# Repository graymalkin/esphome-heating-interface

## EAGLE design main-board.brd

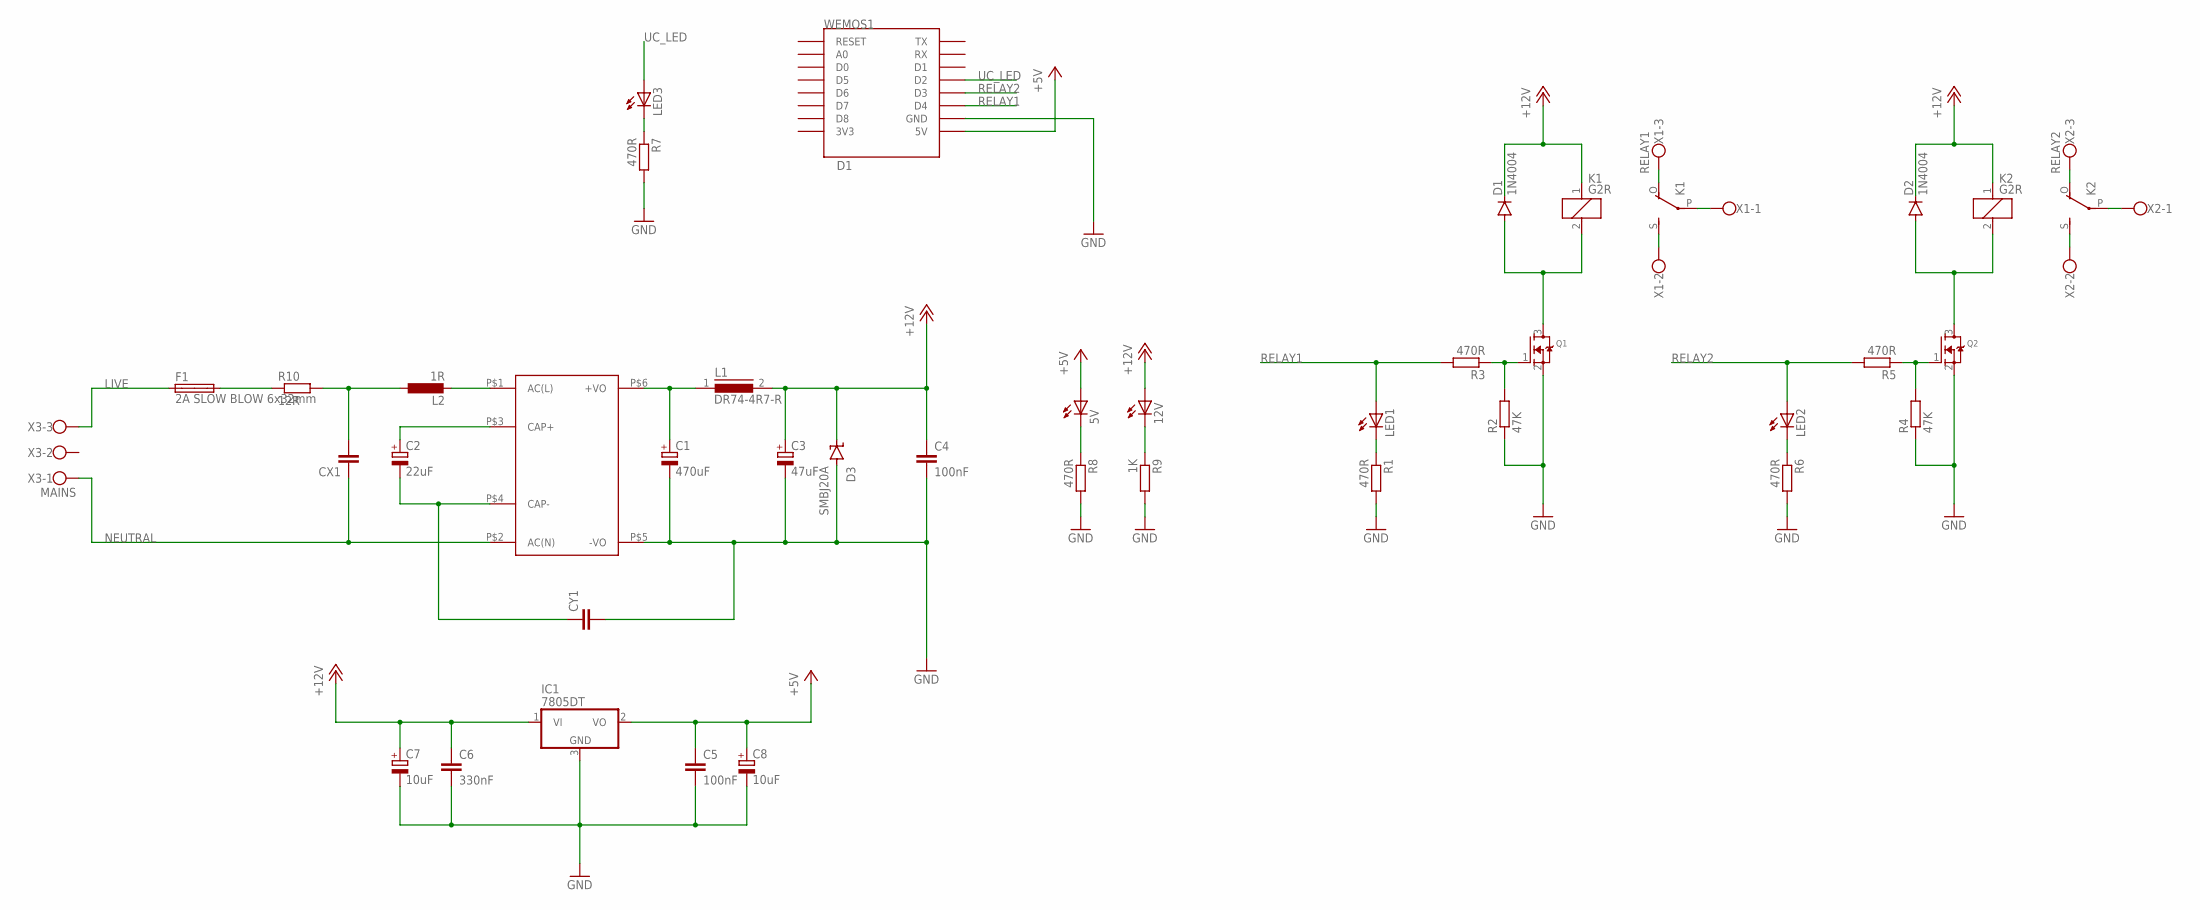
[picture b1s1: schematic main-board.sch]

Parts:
5V, 12V: LEDSMT1206; 1206
C1: 470uF; PANASONIC_E
C2: 22uF; E7,5-16
C3: 47uF; PANASONIC_D
C4, C5: 100nF; C0603
C6: 330nF; C0603
C7, C8: 10uF; PANASONIC_B
CX1: CXXC15B8; XC15B8
CY1: CYYC10B5; YC10B5
D1, D2: 1N4004; DO41-10
D3: SMBJ20A; SMBJ
F1: 2A SLOW BLOW 6x32mm; SH32
IC1: 7805DT; TO252
K1, K2: G2R
L1: DR74-4R7-R; DR74
L2: 1R; 6000-XXXX-RC
LED1, LED2, LED3: LEDSMT1206; 1206
Q1, Q2: MOSFET-NREFLOW; SOT23
R1, R3, R5, R6, R7, R8: 470R; R0603
R2, R4: 47K; R0603
R9: 1K; R0603
R10: 12R; 0922V
U$1: MP-LS05
WEMOS1: D1; WEMOS-D1-MINI
X1: RELAY1; W237-103
X2: RELAY2; W237-103
X3: MAINS; W237-103

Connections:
+5V: 5V.A, C5.1, C8.+, IC1.2 (VO), WEMOS1.5V
+12V: 12V.A, C3.+, C4.1, C6.1, C7.+, D1.C, D2.C, D3.C, IC1.1 (VI), K1.1, K2.1, L1.2
GND: C1.-, C3.-, C4.2, C5.2, C6.2, C7.-, C8.-, CY1.2, D3.A, IC1.3 (GND), Q1.2 (S), Q2.2 (S), R1.2, R2.1, R4.1, R6.2, R7.2, R8.2, R9.2, U$1.P$5 (-VO), WEMOS1.GND
LIVE: F1.1A, X3.3
unnamed: D1.A, K1.2, Q1.3 (D)
unnamed: Q1.1 (G), R2.2, R3.1
unnamed: LED1.C, R1.1
unnamed: K1.O, X1.3
unnamed: K1.P, X1.1
unnamed: K1.S, X1.2
unnamed: D2.A, K2.2, Q2.3 (D)
unnamed: LED2.C, R6.1
unnamed: K2.O, X2.3
unnamed: K2.P, X2.1
unnamed: K2.S, X2.2
unnamed: Q2.1 (G), R4.2, R5.1
unnamed: LED3.C, R7.1
unnamed: 5V.C, R8.1
unnamed: 12V.C, R9.1
unnamed: C1.+, L1.1, U$1.P$6 (+VO)
unnamed: L2.2, U$1.P$1 (AC(L))
unnamed: F1.2A, R10.1
unnamed: C2.+, U$1.P$3 (CAP+)
unnamed: C2.-, CY1.1, U$1.P$4 (CAP-)
unnamed: CX1.2, L2.1, R10.2
NEUTRAL: CX1.1, U$1.P$2 (AC(N)), X3.1
RELAY1: LED1.A, R3.2, WEMOS1.D4
RELAY2: LED2.A, R5.2, WEMOS1.D3
UC_LED: LED3.A, WEMOS1.D2

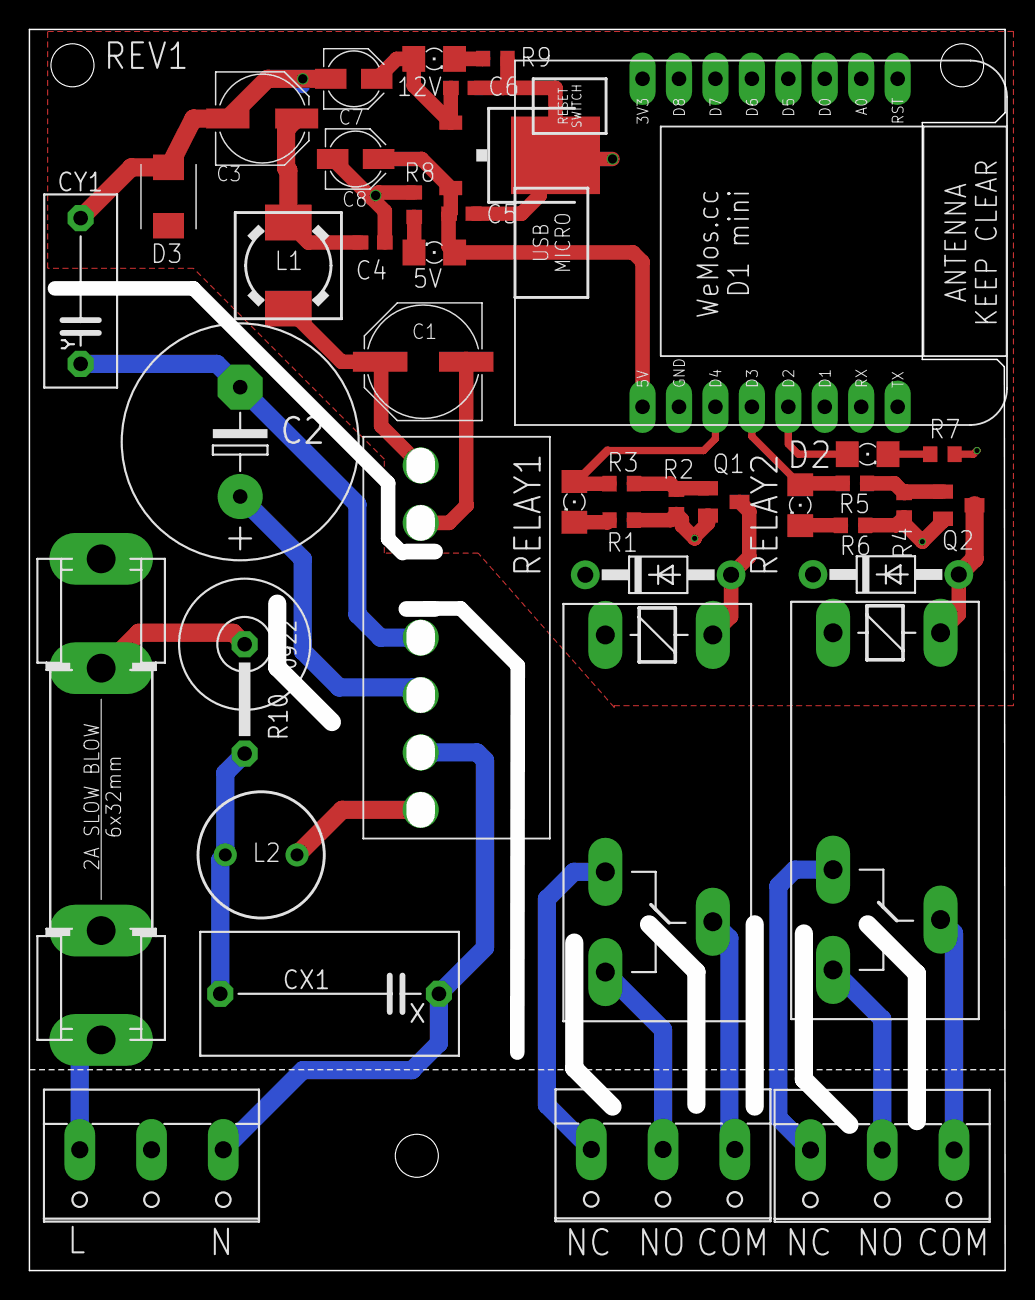
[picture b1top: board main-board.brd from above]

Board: 2 copper layers, 68.0 x 86.5 mm, 41 parts (0 on the bottom side), 29 nets.
